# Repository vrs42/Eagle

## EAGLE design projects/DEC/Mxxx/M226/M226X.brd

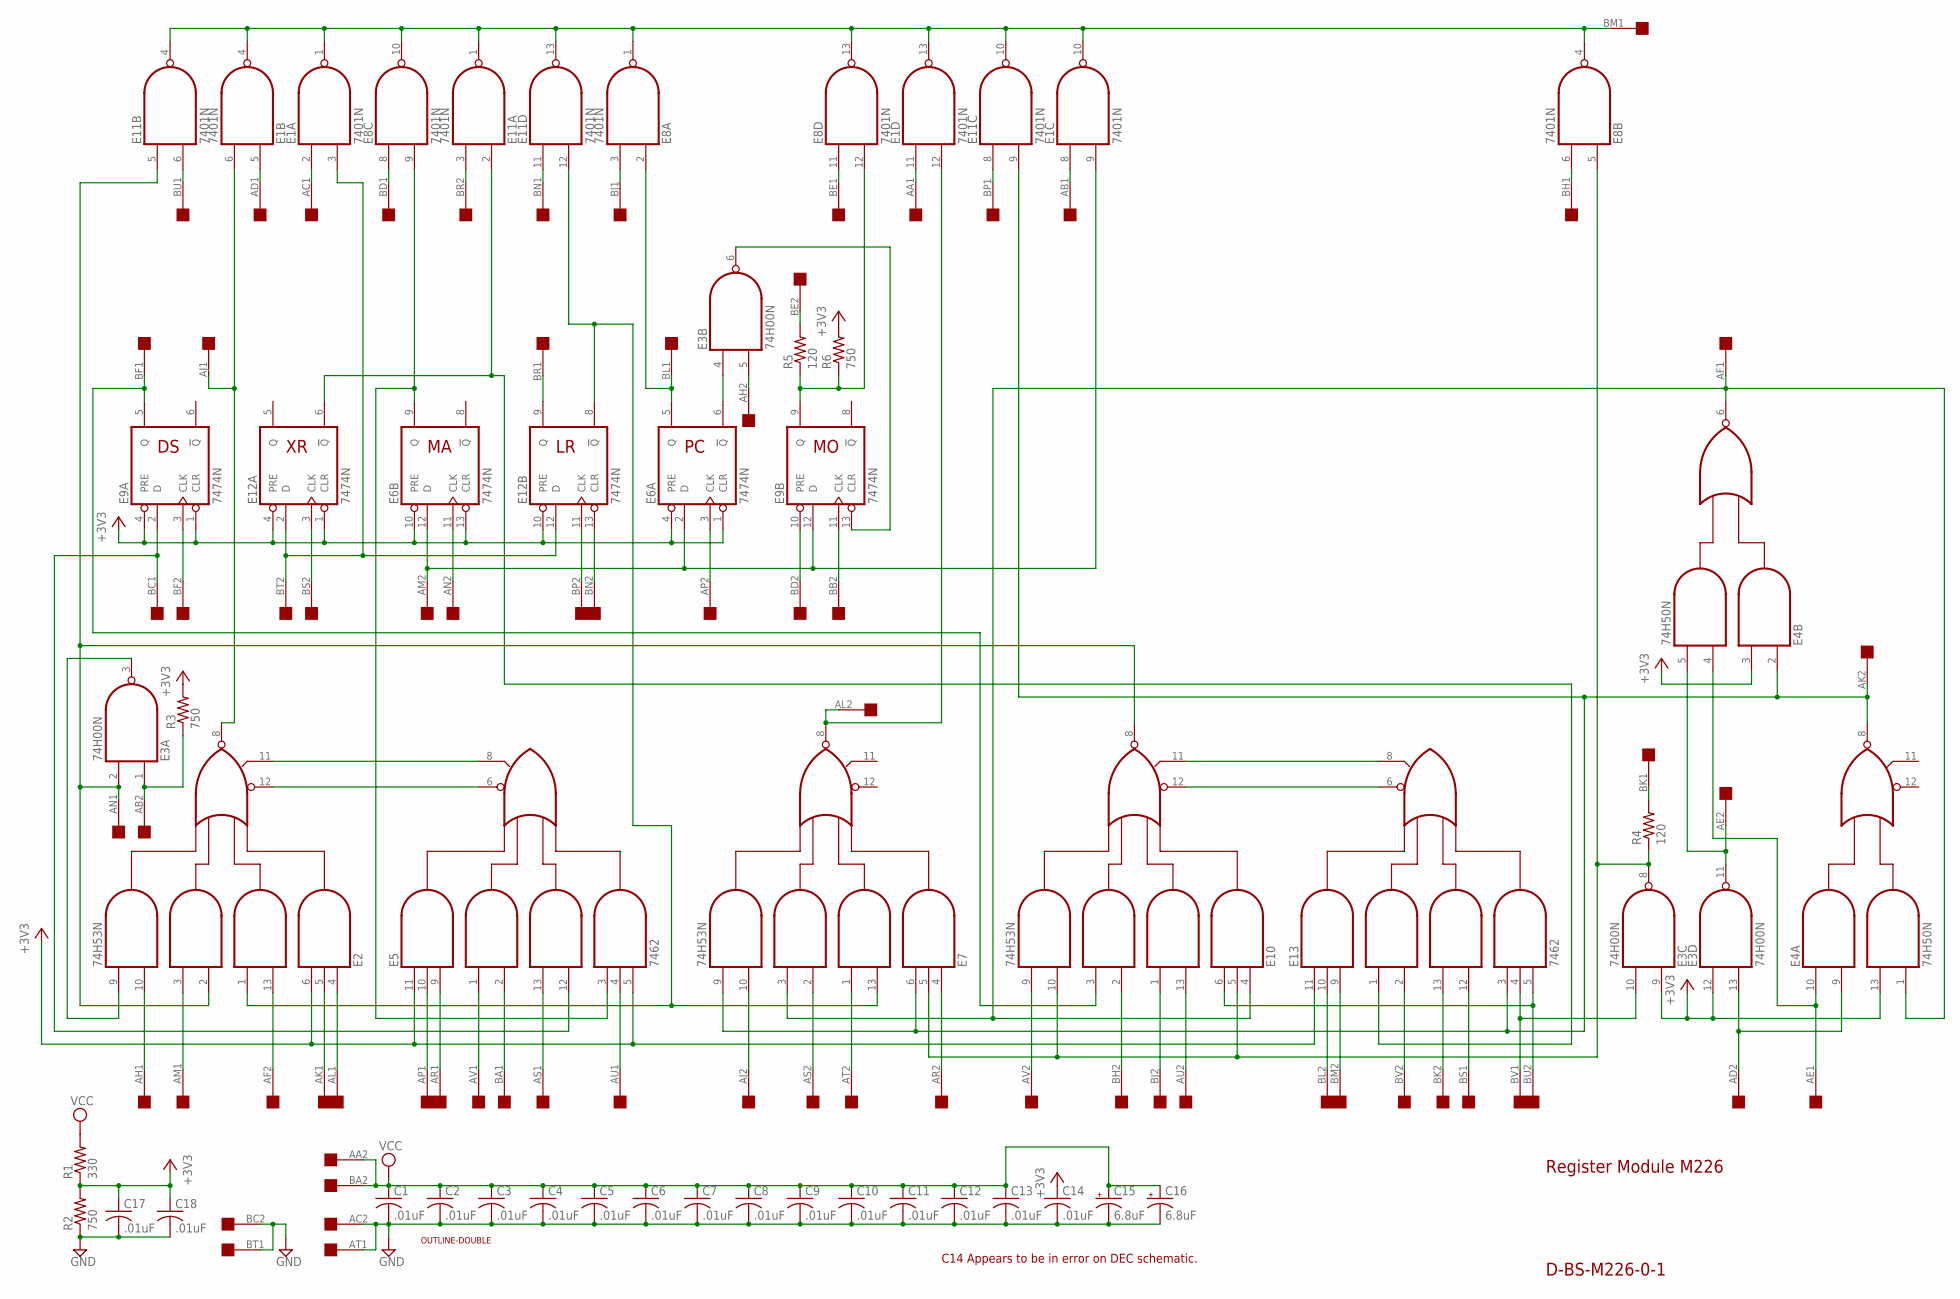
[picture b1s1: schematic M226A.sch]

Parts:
C1, C2, C3, C4, C5, C6, C7, C8, C9, C10, C11, C12, C13, C14, C17, C18: .01uF; C050-025X075
C15, C16: 6.8uF; E12-8
E1, E8, E11: 7401N; DIL14
E2, E7, E10: 74H53N; DIL14
E3: 74H00N; DIL14
E4: 74H50N; DIL14
E5, E13: 7462; DIL14
E6, E9, E12: 7474N; DIL14
R1: 330; 0207/10
R2, R3, R6: 750; 0207/10
R4, R5: 120; 0207/10
U$1: OUTLINE-DOUBLE; DOUBLE
U$3: DOUBLE; EDGE-CON4

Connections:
+3V3: C14.1, C17.1, C18.1, E2.6 (I2), E3.9 (I0), E3.12 (I0), E4.3 (I2), E4.13 (I3), E5.5 (I10), E5.11 (I1), E6.1 (CLR), E6.4 (PRE), E6.10 (PRE), E6.13 (CLR), E9.1 (CLR), E9.4 (PRE), E12.1 (CLR), E12.4 (PRE), E12.10 (PRE), E13.11 (I1), R1.1, R2.2, R3.2, R6.2
GND: C1.2, C2.2, C3.2, C4.2, C5.2, C6.2, C7.2, C8.2, C9.2, C10.2, C11.2, C12.2, C13.2, C14.2, C15.-, C16.-, C17.2, C18.2, E1.7 (GND), E2.7 (GND), E3.7 (GND), E4.7 (GND), E5.7 (GND), E6.7 (GND), E7.7 (GND), E8.7 (GND), E9.7 (GND), E10.7 (GND), E11.7 (GND), E12.7 (GND), E13.7 (GND), R2.1, U$3.AC2, U$3.AT1, U$3.BC2, U$3.BT1
unnamed: E2.12 (I9), E5.6 (E0)
unnamed: E2.11 (I10), E5.8 (E1)
unnamed: E10.11 (I10), E13.8 (E1)
unnamed: E10.12 (I9), E13.6 (E0)
unnamed: E2.10 (I7), U$3.AH1
unnamed: E2.3 (I6), U$3.AM1
unnamed: E2.13 (I3), U$3.AF2
unnamed: E2.4 (I1), U$3.AL1
unnamed: E2.5 (I11), U$3.AK1
unnamed: E5.10 (I2), U$3.AP1
unnamed: E5.9 (I3), U$3.AR1
unnamed: E5.1 (I4), U$3.AV1
unnamed: E5.2 (I5), U$3.BA1
unnamed: E5.13 (I6), U$3.AS1
unnamed: E5.4 (I9), U$3.AU1
unnamed: E2.9 (I8), E3.3 (O)
unnamed: E4.1 (I4), E4.6 (O), E7.3 (I6), E10.4 (I1), U$3.AF1
unnamed: E2.1 (I4), E7.13 (I3), E11.12 (I1), E12.8 (!Q)
unnamed: E11.11 (I0), U$3.BN1
unnamed: E5.3 (I8), E6.9 (Q), E8.9 (I1)
unnamed: E5.12 (I7), E9.2 (D), U$3.BC1
unnamed: E7.10 (I7), U$3.AJ2
unnamed: E7.2 (I5), U$3.AS2
unnamed: E7.1 (I4), U$3.AT2
unnamed: E7.4 (I1), U$3.AR2
unnamed: E10.6 (I2), E13.5 (I10), U$3.BU2
unnamed: E1.3 (I1), E12.2 (D), E12.12 (D), U$3.BT2
unnamed: E4.2 (I1), E4.8 (O), E7.6 (I2), E7.9 (I8), E11.9 (I1), E13.3 (I8), U$3.AK2
unnamed: E3.8 (O), E7.5 (I11), E8.5 (I0), E10.5 (I11), E10.10 (I7), R4.1
unnamed: E8.11 (I0), U$3.BE1
unnamed: E10.9 (I8), U$3.AV2
unnamed: E10.2 (I5), U$3.BH2
unnamed: E10.1 (I4), U$3.BJ2
unnamed: E10.13 (I3), U$3.AU2
unnamed: E3.10 (I1), E13.4 (I9), U$3.BV1
unnamed: E11.2 (I0), E12.6 (!Q), E13.1 (I4)
unnamed: E13.9 (I3), U$3.BM2
unnamed: E13.10 (I2), U$3.BL2
unnamed: E13.2 (I5), U$3.BV2
unnamed: E13.13 (I6), U$3.BK2
unnamed: E13.12 (I7), U$3.BS1
unnamed: E3.13 (I1), E4.9 (I2), U$3.AD2
unnamed: E4.4 (I3), E4.10 (I1), U$3.AE1
unnamed: R4.2, U$3.BK1
unnamed: E3.11 (O), E4.5 (I4), U$3.AE2
unnamed: E9.3 (CLK), U$3.BF2
unnamed: E9.5 (Q), E10.3 (I6), U$3.BF1
unnamed: E12.3 (CLK), U$3.BS2
unnamed: E1.9 (I1), E6.2 (D), E6.12 (D), E9.12 (D), U$3.AM2
unnamed: E6.11 (CLK), U$3.AN2
unnamed: E1.12 (I1), E7.8 (O), U$3.AL2
unnamed: E1.11 (I0), U$3.AA1
unnamed: E12.9 (Q), U$3.BR1
unnamed: E12.13 (CLR), U$3.BN2
unnamed: E12.11 (CLK), U$3.BP2
unnamed: E8.12 (I1), E9.9 (Q), R5.1, R6.1
unnamed: E6.3 (CLK), U$3.AP2
unnamed: E9.10 (PRE), U$3.BD2
unnamed: E9.11 (CLK), U$3.BB2
unnamed: E3.6 (O), E9.13 (CLR)
unnamed: E3.5 (I1), U$3.AH2
unnamed: E6.5 (Q), E8.2 (I0), U$3.BL1
unnamed: E3.4 (I0), E6.6 (!Q)
unnamed: R5.2, U$3.BE2
unnamed: E3.1 (I0), R3.1, U$3.AB2
unnamed: E2.2 (I5), E3.2 (I1), E10.8 (O), E11.5 (I0), U$3.AN1
unnamed: E11.6 (I1), U$3.BU1
unnamed: E1.6 (I1), E2.8 (O), U$3.AJ1
unnamed: E1.5 (I0), U$3.AD1
unnamed: E1.1 (O), E1.4 (O), E1.10 (O), E1.13 (O), E8.1 (O), E8.4 (O), E8.10 (O), E8.13 (O), E11.1 (O), E11.4 (O), E11.10 (O), E11.13 (O), U$3.BM1
unnamed: E1.2 (I0), U$3.AC1
unnamed: E8.8 (I0), U$3.BD1
unnamed: E8.3 (I1), U$3.BJ1
unnamed: E11.8 (I0), U$3.BP1
unnamed: E11.3 (I1), U$3.BR2
unnamed: E8.6 (I1), U$3.BH1
unnamed: E1.8 (I0), U$3.AB1
VCC: C1.1, C2.1, C3.1, C4.1, C5.1, C6.1, C7.1, C8.1, C9.1, C10.1, C11.1, C12.1, C13.1, C15.+, C16.+, E1.14 (VCC), E2.14 (VCC), E3.14 (VCC), E4.14 (VCC), E5.14 (VCC), E6.14 (VCC), E7.14 (VCC), E8.14 (VCC), E9.14 (VCC), E10.14 (VCC), E11.14 (VCC), E12.14 (VCC), E13.14 (VCC), R1.2, U$3.AA2, U$3.BA2

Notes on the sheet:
Register Module M226
D-BS-M226-0-1
C14 Appears to be in error on DEC schematic.

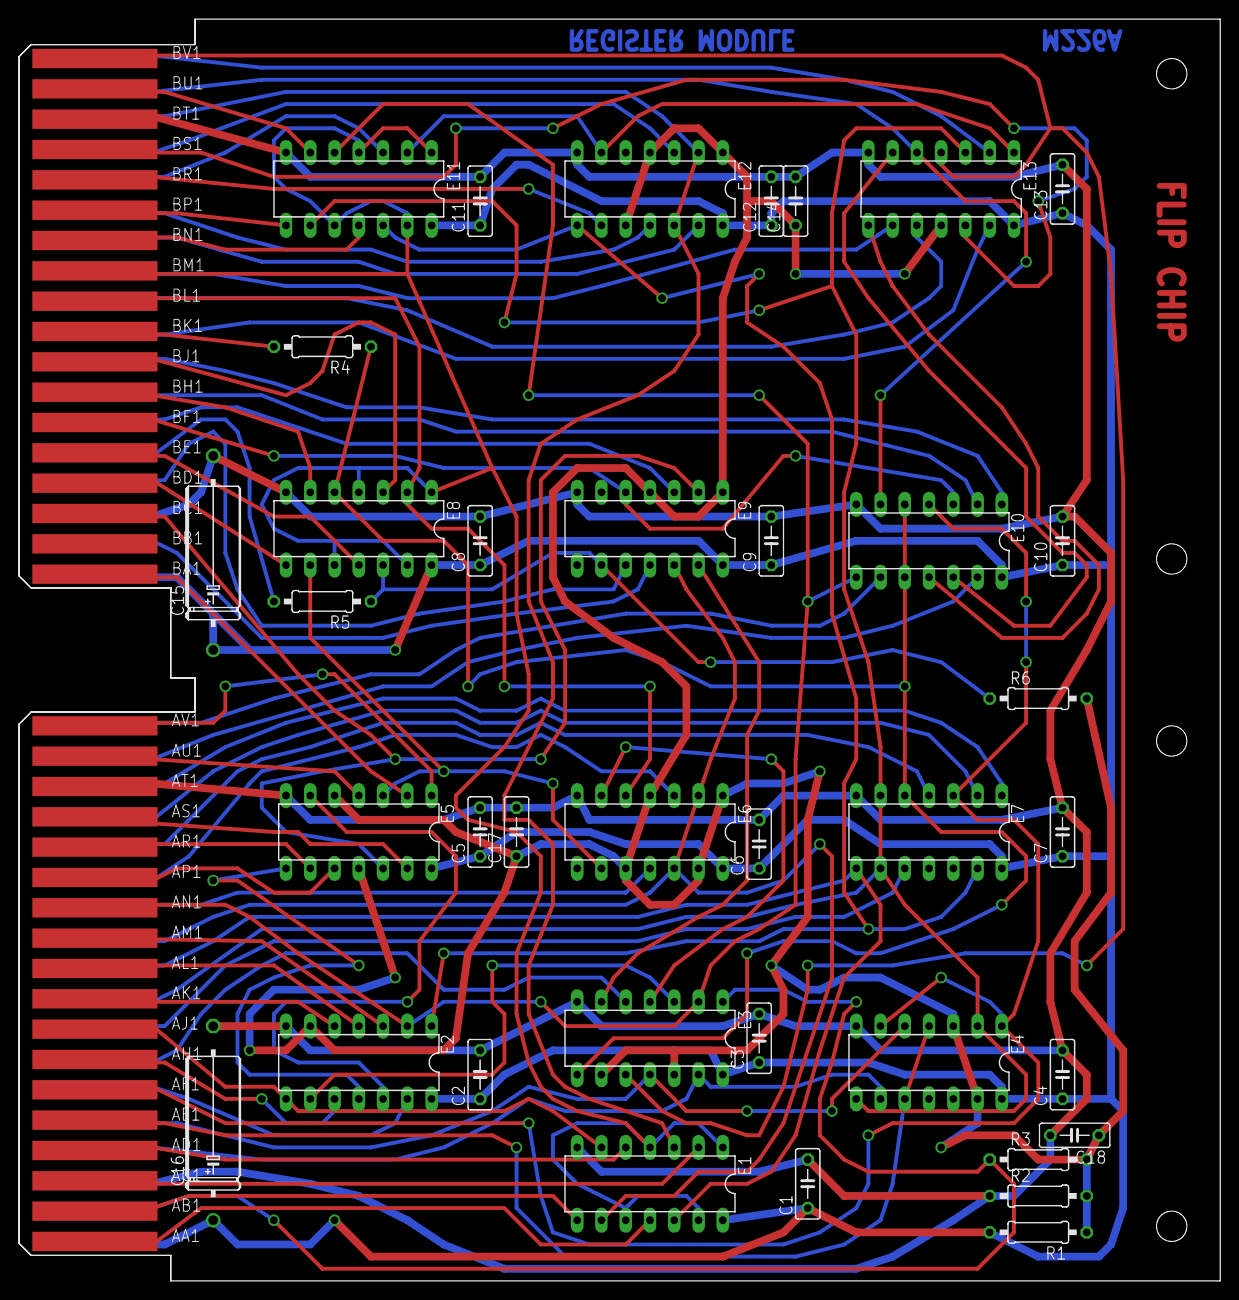
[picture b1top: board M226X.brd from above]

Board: 2 copper layers, 125.7 x 132.1 mm, 39 parts (0 on the bottom side), 80 nets.

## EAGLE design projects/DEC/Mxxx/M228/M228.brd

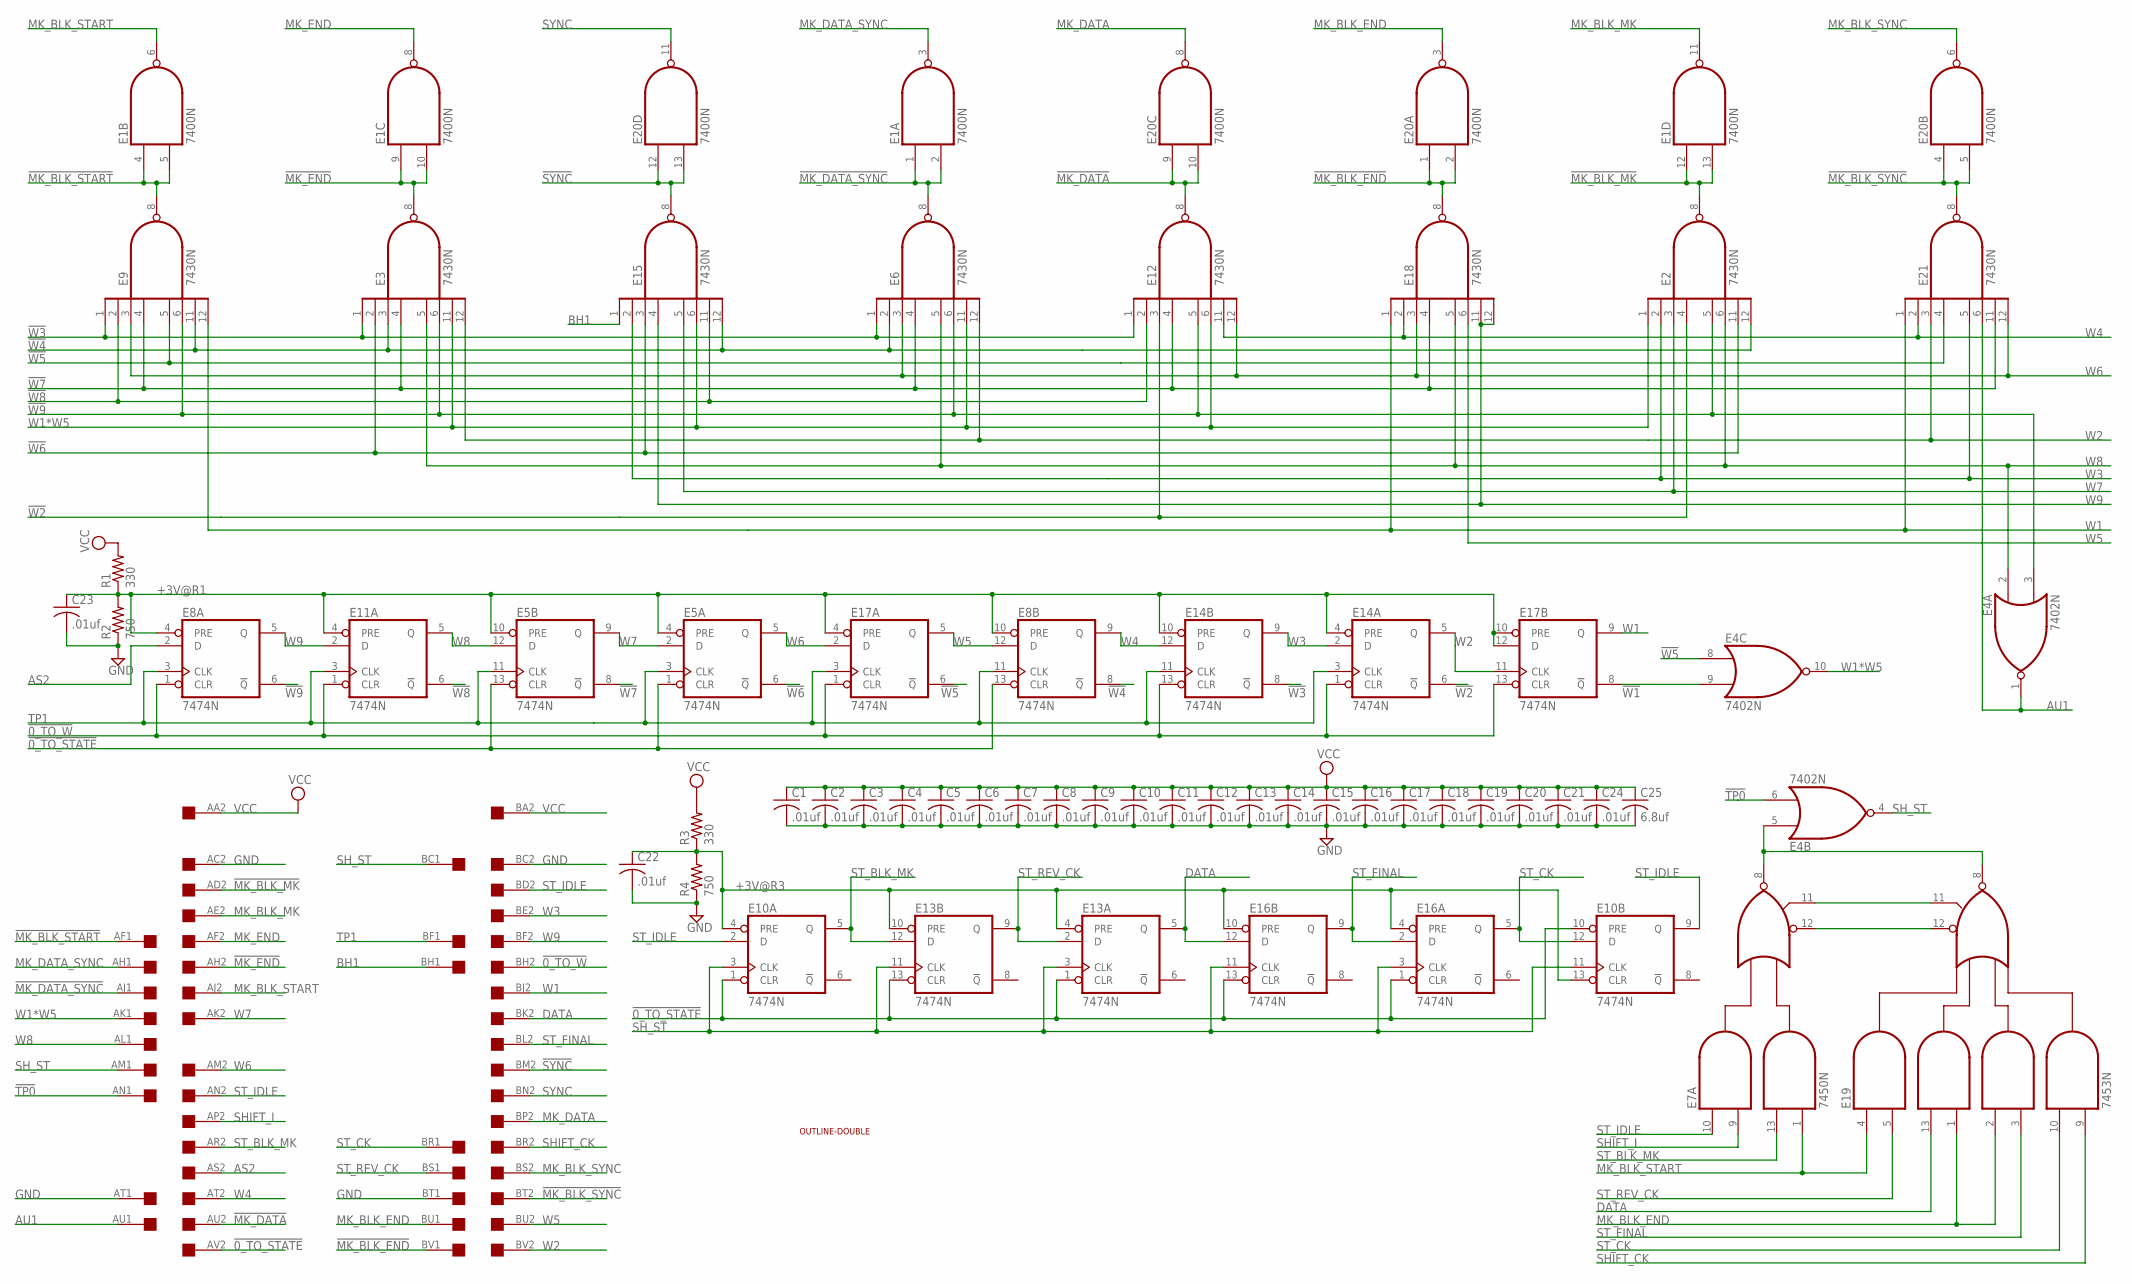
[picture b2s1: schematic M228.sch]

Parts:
C1, C2, C3, C4, C5, C6, C7, C8, C9, C10, C11, C12, C13, C14, C15, C16, C17, C18, C19, C20, C21, C22, C23, C24: .01uf; C050-025X075
C25: 6.8uf; C150-054X183
E1, E20: 7400N; DIL14
E2, E3, E6, E9, E12, E15, E18, E21: 7430N; DIL14
E4: 7402N; DIL14
E5, E8, E10, E11, E13, E14, E16, E17: 7474N; DIL14
E7: 7450N; DIL14
E19: 7453N; DIL14
R1, R3: 330; 0207/10
R2, R4: 750; 0207/10
U$1: OUTLINE-DOUBLE; DOUBLE
U$5: DOUBLE; EDGE-CON4

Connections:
!0_TO_STATE: E5.1 (CLR), E5.13 (CLR), E8.13 (CLR), E10.1 (CLR), E10.10 (PRE), E13.1 (CLR), E13.13 (CLR), E16.1 (CLR), E16.13 (CLR), U$5.AV2
!0_TO_W: E8.1 (CLR), E11.1 (CLR), E14.1 (CLR), E14.13 (CLR), E17.1 (CLR), E17.13 (CLR), U$5.BH2
!MK_BLK_END: E18.8 (O), E20.1 (I0), E20.2 (I1), U$5.BV1
!MK_BLK_MK: E1.12 (I0), E1.13 (I1), E2.8 (O), U$5.AD2
!MK_BLK_START: E1.4 (I0), E1.5 (I1), E9.8 (O), U$5.AF1
!MK_BLK_SYNC: E20.4 (I0), E20.5 (I1), E21.8 (O), U$5.BT2
!MK_DATA: E12.8 (O), E20.9 (I0), E20.10 (I1), U$5.AU2
!MK_DATA_SYNC: E1.1 (I0), E1.2 (I1), E6.8 (O), U$5.AJ1
!MK_END: E1.9 (I0), E1.10 (I1), E3.8 (O), U$5.AH2
!SYNC: E15.8 (O), E20.12 (I0), E20.13 (I1), U$5.BM2
!TP0: E4.6 (I1), U$5.AN1
!W1: E4.9 (I1), E17.8 (!Q)
!W2: E2.4 (I3), E12.3 (I2), E14.6 (!Q)
!W3: E3.1 (I0), E6.1 (I0), E9.1 (I0), E12.1 (I0), E14.8 (!Q)
!W4: E2.12 (I7), E3.3 (I2), E6.2 (I1), E8.8 (!Q), E9.11 (I6), E15.12 (I7)
!W5: E4.8 (I0), E9.5 (I4), E17.6 (!Q), E21.4 (I3)
!W6: E2.11 (I6), E3.2 (I1), E5.6 (!Q), E15.3 (I2)
!W7: E3.4 (I3), E5.8 (!Q), E6.4 (I3), E9.4 (I3), E12.4 (I3), E18.4 (I3), E21.11 (I6)
!W8: E9.2 (I1), E11.6 (!Q), E12.2 (I1), E15.11 (I6)
!W9: E2.5 (I4), E3.6 (I5), E4.3 (I1), E6.6 (I5), E8.6 (!Q), E9.6 (I5), E12.5 (I4)
+3V@R1: C23.1, E5.4 (PRE), E5.10 (PRE), E8.4 (PRE), E8.10 (PRE), E11.4 (PRE), E14.4 (PRE), E14.10 (PRE), E17.4 (PRE), E17.10 (PRE), E17.12 (D), R1.1, R2.2
+3V@R3: C22.1, E10.4 (PRE), E10.13 (CLR), E13.4 (PRE), E13.10 (PRE), E16.4 (PRE), E16.10 (PRE), R3.1, R4.2
AS2: E8.2 (D), U$5.AS2
AU1: E4.1 (O), E21.6 (I5), U$5.AU1
BH1: E15.1 (I0), U$5.BH1
DATA: E13.5 (Q), E16.12 (D), E19.13 (I3), U$5.BK2
GND: C1.2, C2.2, C3.2, C4.2, C5.2, C6.2, C7.2, C8.2, C9.2, C10.2, C11.2, C12.2, C13.2, C14.2, C15.2, C16.2, C17.2, C18.2, C19.2, C20.2, C21.2, C22.2, C23.2, C24.2, C25.2, E1.7 (GND), E2.7 (GND), E3.7 (GND), E4.7 (GND), E5.7 (GND), E6.7 (GND), E7.7 (GND), E8.7 (GND), E9.7 (GND), E10.7 (GND), E11.7 (GND), E12.7 (GND), E13.7 (GND), E14.7 (GND), E15.7 (GND), E16.7 (GND), E17.7 (GND), E18.7 (GND), E19.7 (GND), E20.7 (GND), E21.7 (GND), R2.1, R4.1, U$5.AC2, U$5.AT1, U$5.BC2, U$5.BT1
MK_BLK_END: E19.1 (I4), E19.2 (I5), E20.3 (O), U$5.BU1
MK_BLK_MK: E1.11 (O), U$5.AE2
MK_BLK_START: E1.6 (O), E7.1 (I4), E19.4 (I1), U$5.AJ2
MK_BLK_SYNC: E20.6 (O), U$5.BS2
MK_DATA: E20.8 (O), U$5.BP2
MK_DATA_SYNC: E1.3 (O), U$5.AH1
MK_END: E1.8 (O), U$5.AF2
unnamed: E7.12 (I5), E19.12 (I9)
unnamed: E7.11 (I6), E19.11 (I10)
unnamed: E4.5 (I0), E7.8 (O), E19.8 (O)
SHIFT_CK: E19.9 (I8), U$5.BR2
SHIFT_I: E7.9 (I2), U$5.AP2
SH_ST: E4.4 (O), E10.3 (CLK), E10.11 (CLK), E13.3 (CLK), E13.11 (CLK), E16.3 (CLK), E16.11 (CLK), U$5.AM1, U$5.BC1
ST_BLK_MK: E7.13 (I3), E10.5 (Q), E13.12 (D), U$5.AR2
ST_CK: E10.12 (D), E16.5 (Q), E19.10 (I7), U$5.BR1
ST_FINAL: E16.2 (D), E16.9 (Q), E19.3 (I6), U$5.BL2
ST_IDLE: E7.10 (I1), E10.2 (D), E10.9 (Q), U$5.AN2, U$5.BD2
ST_REV_CK: E13.2 (D), E13.9 (Q), E19.5 (I2), U$5.BS1
SYNC: E20.11 (O), U$5.BN2
TP1: E5.3 (CLK), E5.11 (CLK), E8.3 (CLK), E8.11 (CLK), E11.3 (CLK), E14.3 (CLK), E14.11 (CLK), E17.3 (CLK), U$5.BF1
VCC: C1.1, C2.1, C3.1, C4.1, C5.1, C6.1, C7.1, C8.1, C9.1, C10.1, C11.1, C12.1, C13.1, C14.1, C15.1, C16.1, C17.1, C18.1, C19.1, C20.1, C21.1, C24.1, C25.1, E1.14 (VCC), E2.14 (VCC), E3.14 (VCC), E4.14 (VCC), E5.14 (VCC), E6.14 (VCC), E7.14 (VCC), E8.14 (VCC), E9.14 (VCC), E10.14 (VCC), E11.14 (VCC), E12.14 (VCC), E13.14 (VCC), E14.14 (VCC), E15.14 (VCC), E16.14 (VCC), E17.14 (VCC), E18.14 (VCC), E19.14 (VCC), E20.14 (VCC), E21.14 (VCC), R1.2, R3.2, U$5.AA2, U$5.BA2
W1: E9.12 (I7), E17.9 (Q), E18.1 (I0), E21.1 (I0), U$5.BJ2
W1*W5: E2.1 (I0), E3.11 (I6), E4.10 (O), E6.11 (I6), E12.6 (I5), E15.6 (I5), U$5.AK1
W2: E3.12 (I7), E6.12 (I7), E14.5 (Q), E17.11 (CLK), E21.3 (I2), U$5.BV2
W3: E2.2 (I1), E14.2 (D), E14.9 (Q), E15.2 (I1), E21.5 (I4), U$5.BE2
W4: E8.9 (Q), E12.11 (I6), E14.12 (D), E18.2 (I1), E21.2 (I1), U$5.AT2
W5: E8.12 (D), E17.5 (Q), E18.6 (I5), U$5.BU2
W6: E5.5 (Q), E6.3 (I2), E9.3 (I2), E12.12 (I7), E17.2 (D), E18.3 (I2), E21.12 (I7), U$5.AM2
W7: E2.3 (I2), E5.2 (D), E5.9 (Q), E15.5 (I4), U$5.AK2
W8: E2.6 (I5), E3.5 (I4), E4.2 (I0), E5.12 (D), E6.5 (I4), E11.5 (Q), E18.5 (I4), U$5.AL1
W9: E8.5 (Q), E11.2 (D), E15.4 (I3), E18.11 (I6), E18.12 (I7), U$5.BF2

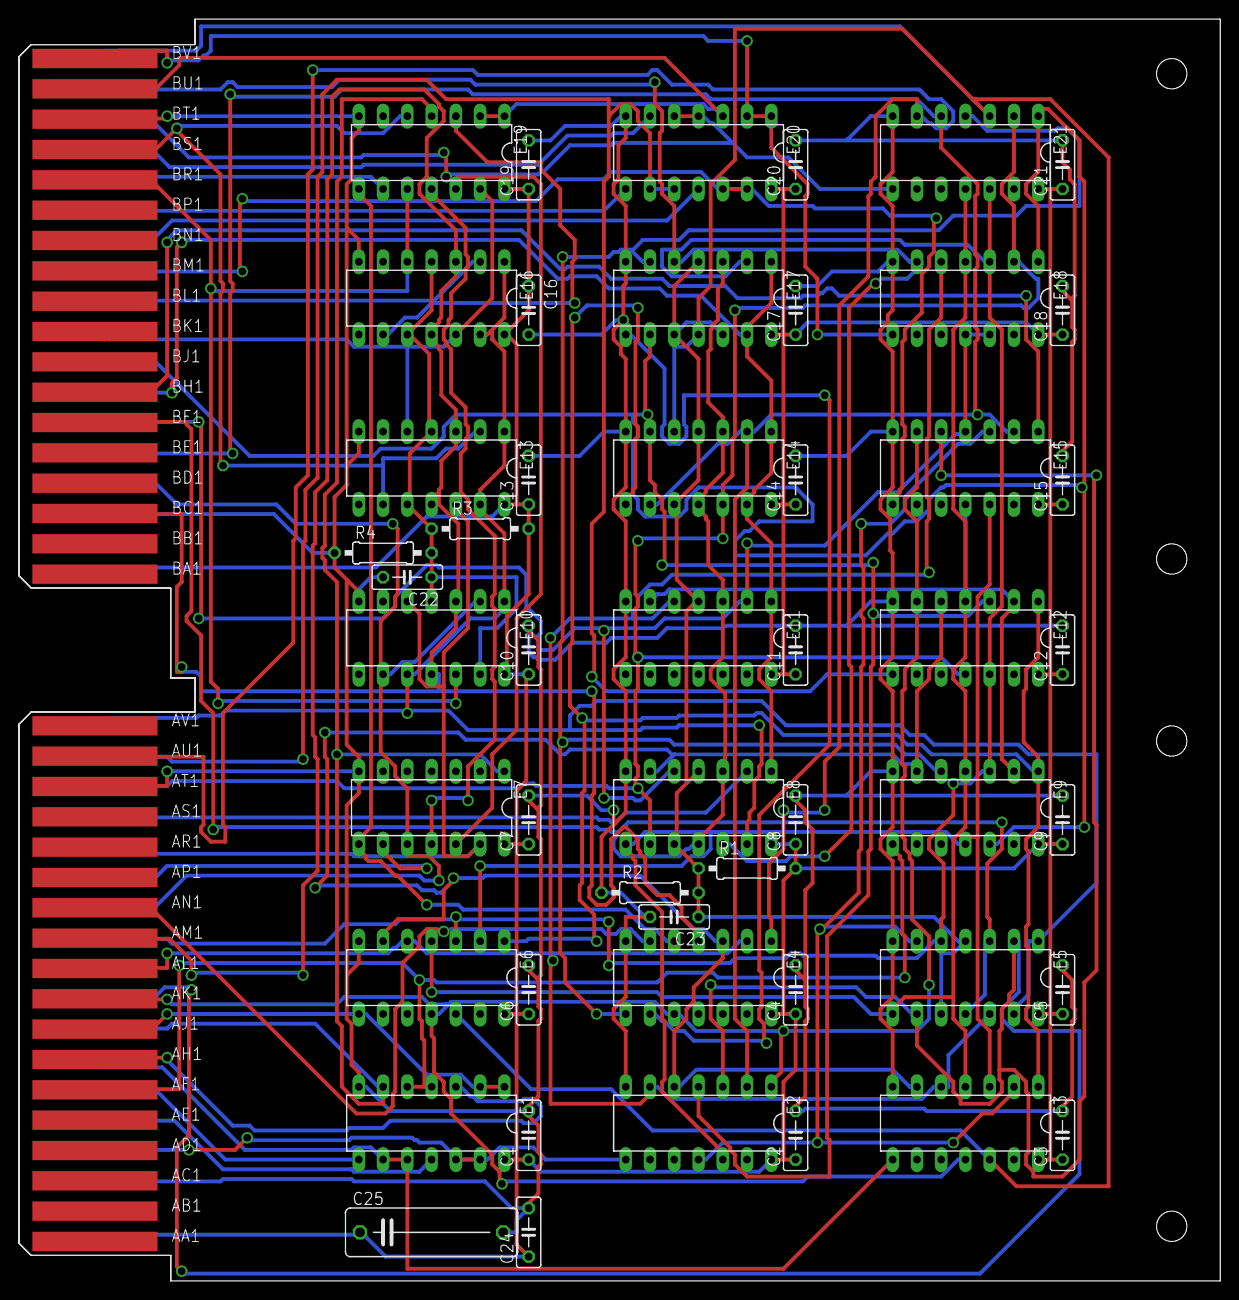
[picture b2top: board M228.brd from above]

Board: 2 copper layers, 125.7 x 132.1 mm, 52 parts (0 on the bottom side), 58 nets.

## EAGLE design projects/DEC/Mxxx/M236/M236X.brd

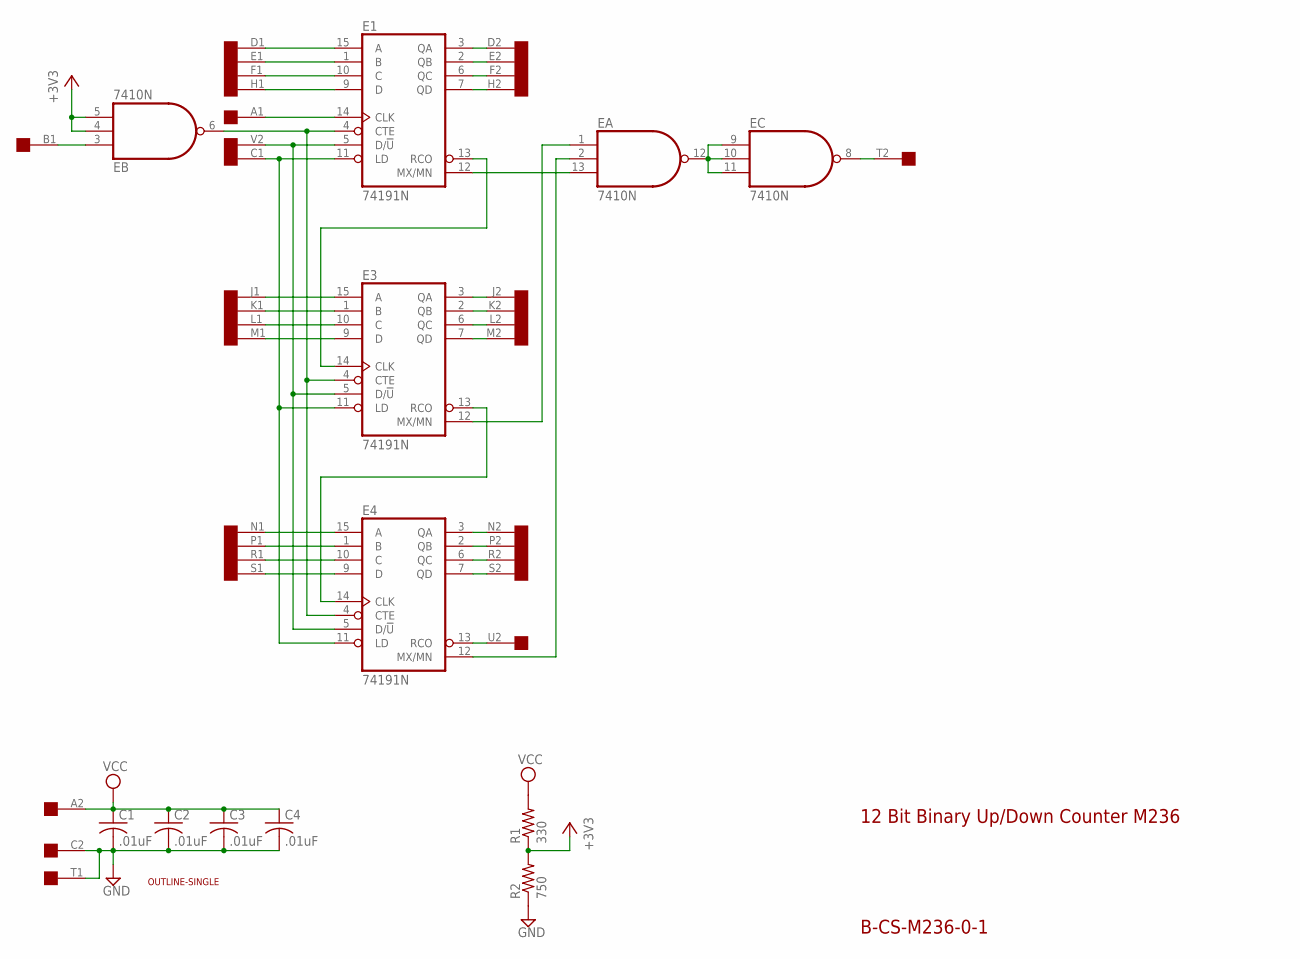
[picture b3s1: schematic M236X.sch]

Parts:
C1, C2, C3, C4: .01uF; C050-025X075
E: 7410N; DIL14
E1, E3, E4: 74191N; DIL16
R1: 330; 0207/10
R2: 750; 0207/10
U$1: OUTLINE-SINGLE; SINGLE
U$2: SINGLE; EDGE-CON2

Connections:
+3V3: E.4 (I1), E.5 (I2), R1.1, R2.2
GND: C1.2, C2.2, C3.2, C4.2, E.7 (GND), E1.8 (GND), E3.8 (GND), E4.8 (GND), R2.1, U$2.C2, U$2.T1
unnamed: E1.7 (QD), U$2.H2
unnamed: E1.6 (QC), U$2.F2
unnamed: E1.2 (QB), U$2.E2
unnamed: E1.3 (QA), U$2.D2
unnamed: E1.9 (D), U$2.H1
unnamed: E1.10 (C), U$2.F1
unnamed: E1.1 (B), U$2.E1
unnamed: E1.15 (A), U$2.D1
unnamed: E3.6 (QC), U$2.L2
unnamed: E3.7 (QD), U$2.M2
unnamed: E4.3 (QA), U$2.N2
unnamed: E4.2 (QB), U$2.P2
unnamed: E4.6 (QC), U$2.R2
unnamed: E4.7 (QD), U$2.S2
unnamed: E3.2 (QB), U$2.K2
unnamed: E3.3 (QA), U$2.J2
unnamed: E4.9 (D), U$2.S1
unnamed: E4.10 (C), U$2.R1
unnamed: E4.1 (B), U$2.P1
unnamed: E4.15 (A), U$2.N1
unnamed: E3.9 (D), U$2.M1
unnamed: E3.10 (C), U$2.L1
unnamed: E3.1 (B), U$2.K1
unnamed: E3.15 (A), U$2.J1
unnamed: E1.11 (LD), E3.11 (LD), E4.11 (LD), U$2.C1
unnamed: E1.5 (D/!U), E3.5 (D/!U), E4.5 (D/!U), U$2.V2
unnamed: E4.13 (RCO), U$2.U2
unnamed: E.8 (O), U$2.T2
unnamed: E.6 (O), E1.4 (CTE), E3.4 (CTE), E4.4 (CTE)
unnamed: E3.13 (RCO), E4.14 (CLK)
unnamed: E.3 (I0), U$2.B1
unnamed: E.2 (I1), E4.12 (MX/MN)
unnamed: E.1 (I0), E3.12 (MX/MN)
unnamed: E.9 (I0), E.10 (I1), E.11 (I2), E.12 (O)
unnamed: E.13 (I2), E1.12 (MX/MN)
unnamed: E1.14 (CLK), U$2.A1
unnamed: E1.13 (RCO), E3.14 (CLK)
VCC: C1.1, C2.1, C3.1, C4.1, E.14 (VCC), E1.16 (VCC), E3.16 (VCC), E4.16 (VCC), R1.2, U$2.A2

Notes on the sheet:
B-CS-M236-0-1
12 Bit Binary Up/Down Counter M236

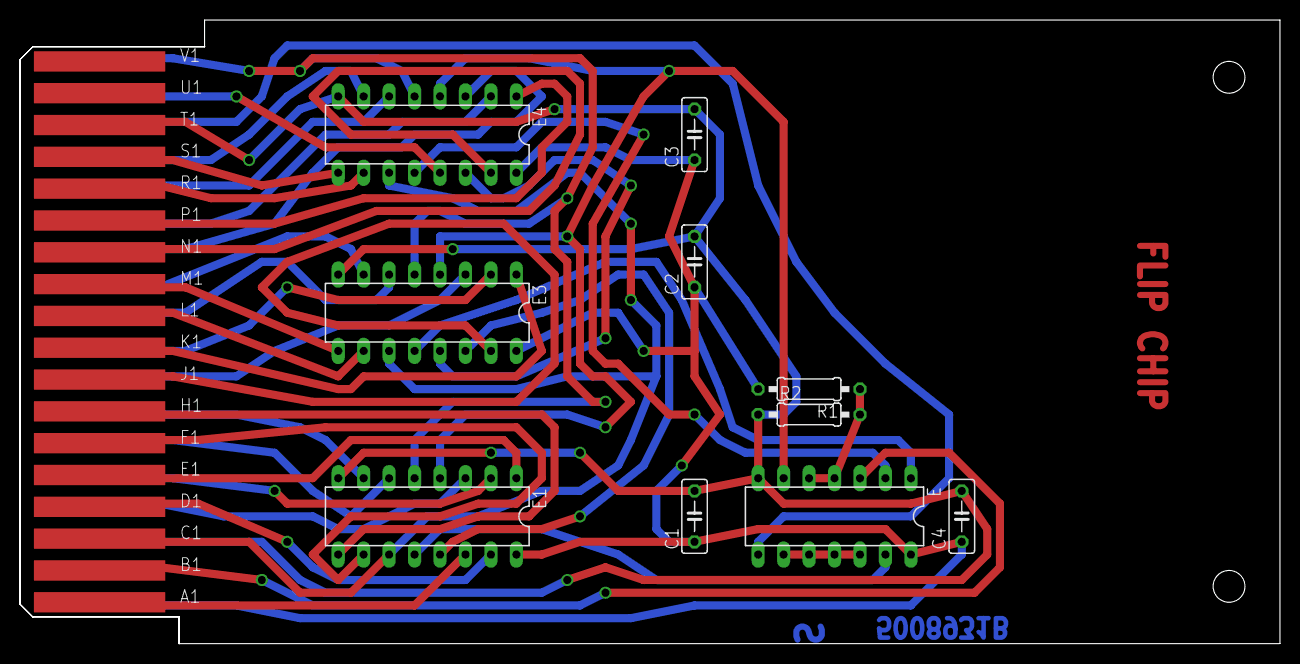
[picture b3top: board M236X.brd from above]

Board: 2 copper layers, 125.7 x 62.2 mm, 12 parts (0 on the bottom side), 40 nets.

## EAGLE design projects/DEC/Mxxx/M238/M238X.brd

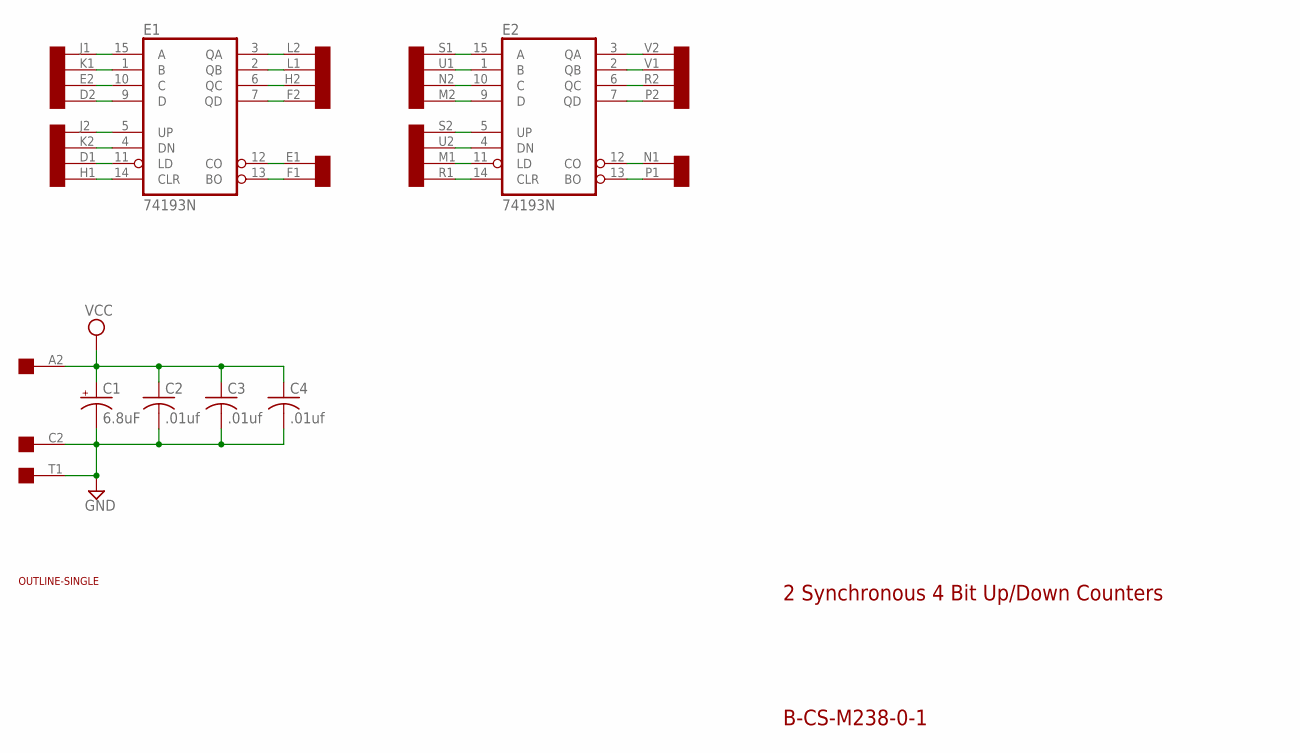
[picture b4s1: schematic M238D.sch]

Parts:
C1: 6.8uF; E12-8
C2, C3, C4: .01uf; C050-025X075
E1, E2: 74193N; DIL16
U$1: OUTLINE-SINGLE; SINGLE
U$2: SINGLE; EDGE-CON2

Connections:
D1: E1.11 (LD), U$2.D1
D2: E1.9 (D), U$2.D2
E1: E1.12 (CO), U$2.E1
E2: E1.10 (C), U$2.E2
F1: E1.13 (BO), U$2.F1
F2: E1.7 (QD), U$2.F2
GND: C1.-, C2.2, C3.2, C4.2, E1.8 (GND), E2.8 (GND), U$2.C2, U$2.T1
H1: E1.14 (CLR), U$2.H1
H2: E1.6 (QC), U$2.H2
J1: E1.15 (A), U$2.J1
J2: E1.5 (UP), U$2.J2
K1: E1.1 (B), U$2.K1
K2: E1.4 (DN), U$2.K2
L1: E1.2 (QB), U$2.L1
L2: E1.3 (QA), U$2.L2
M1: E2.11 (LD), U$2.M1
M2: E2.9 (D), U$2.M2
N1: E2.12 (CO), U$2.N1
N2: E2.10 (C), U$2.N2
P1: E2.13 (BO), U$2.P1
P2: E2.7 (QD), U$2.P2
R1: E2.14 (CLR), U$2.R1
R2: E2.6 (QC), U$2.R2
S1: E2.15 (A), U$2.S1
S2: E2.5 (UP), U$2.S2
U1: E2.1 (B), U$2.U1
U2: E2.4 (DN), U$2.U2
V1: E2.2 (QB), U$2.V1
V2: E2.3 (QA), U$2.V2
VCC: C1.+, C2.1, C3.1, C4.1, E1.16 (VCC), E2.16 (VCC), U$2.A2

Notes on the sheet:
2 Synchronous 4 Bit Up/Down Counters
B-CS-M238-0-1

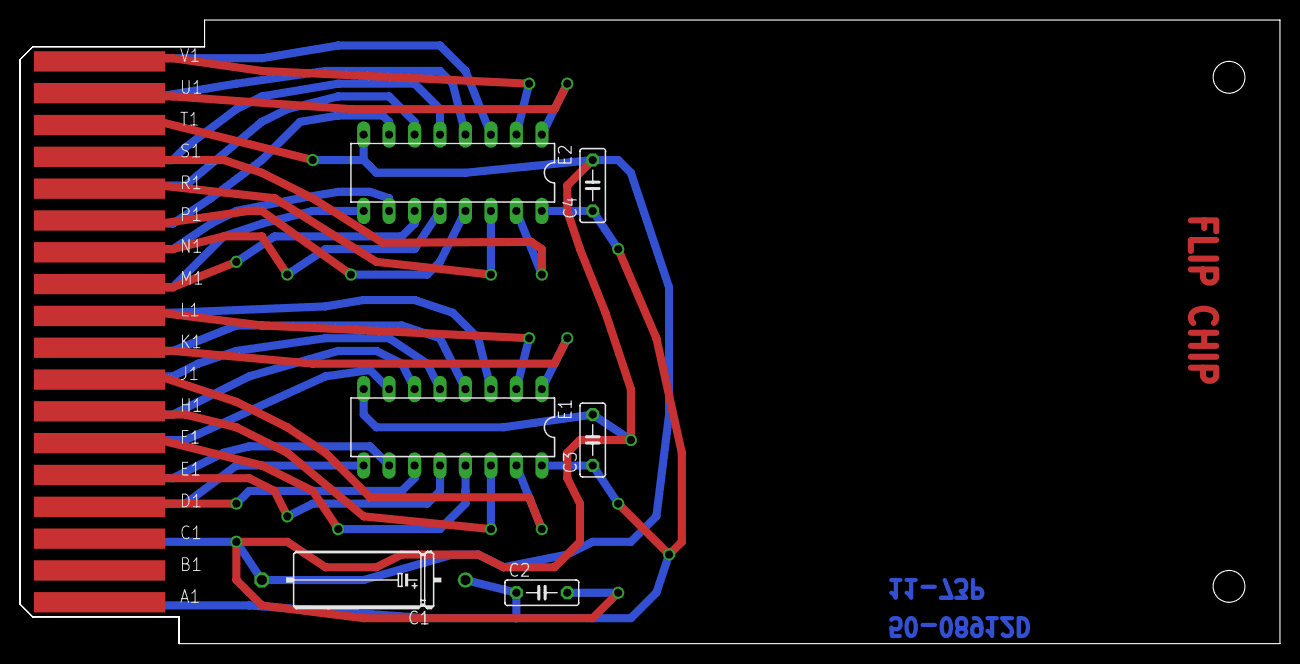
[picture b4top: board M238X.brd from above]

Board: 2 copper layers, 125.7 x 62.2 mm, 8 parts (0 on the bottom side), 30 nets.
